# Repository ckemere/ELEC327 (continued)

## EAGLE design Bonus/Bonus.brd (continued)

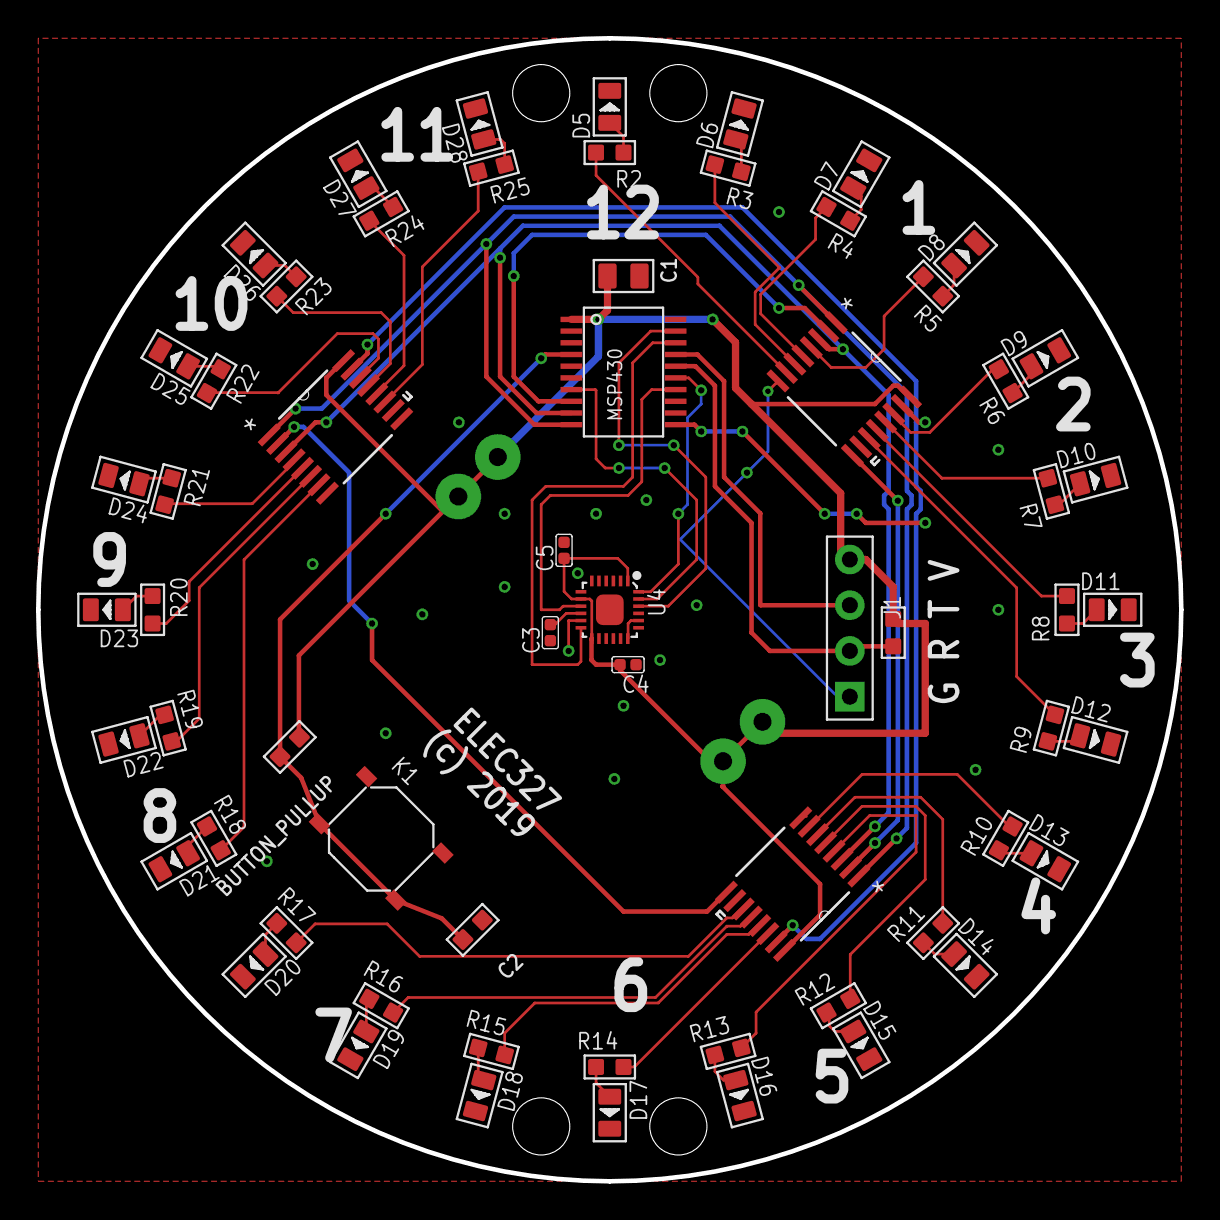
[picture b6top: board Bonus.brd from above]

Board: 2 copper layers, 63.5 x 63.5 mm, 63 parts (1 on the bottom side), 65 nets.

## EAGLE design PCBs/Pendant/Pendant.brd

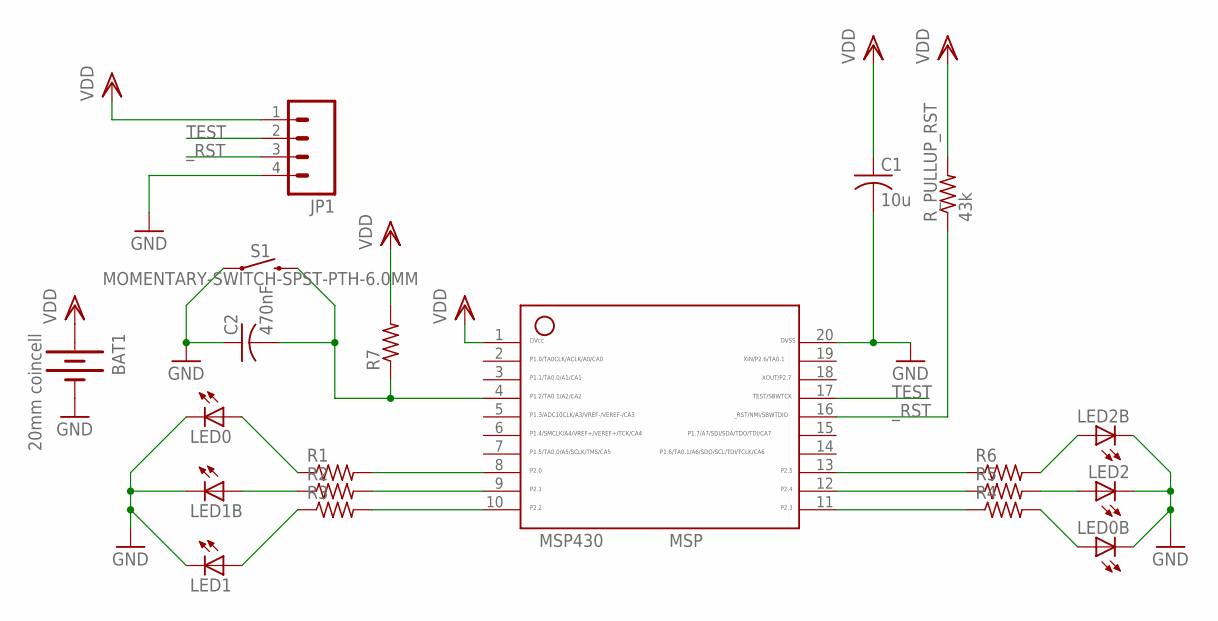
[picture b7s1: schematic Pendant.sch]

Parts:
BAT1: 20mm coincell; BATTCON_20MM_PTH_COMPACT
C1: 10u; C1206
C2: 470nF; C1206
JP1: M04LOCK; 1X04_LOCK
LED0, LED0B, LED1, LED1B, LED2, LED2B: LED1206; LED-1206
MSP430: MSP; 20_PIN
R1, R2, R3, R4, R5, R6, R7: R-US_R1206; R1206
R_PULLUP_RST: 43k; R1206
S1: MOMENTARY-SWITCH-SPST-PTH-6.0MM; TACTILE_SWITCH_PTH_6.0MM

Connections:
GND: BAT1.2 (-), C1.2, C2.1, JP1.4, LED0.C, LED0B.C, LED1.C, LED1B.C, LED2.C, LED2B.C, MSP430.20, S1.1
unnamed: MSP430.12, R5.1
unnamed: MSP430.11, R4.1
unnamed: LED2.A, R5.2
unnamed: LED0B.A, R4.2
unnamed: MSP430.13, R6.1
unnamed: LED0.A, R1.1
unnamed: LED1B.A, R2.1
unnamed: LED2B.A, R6.2
unnamed: LED1.A, R3.1
unnamed: MSP430.8, R1.2
unnamed: MSP430.9, R2.2
unnamed: MSP430.10, R3.2
unnamed: C2.2, MSP430.4, R7.1, S1.3 (2)
TEST: JP1.2, MSP430.17
VDD: BAT1.1 (+), BAT1.3 (+), BAT1.4 (+), BAT1.5 (+), C1.1, JP1.1, MSP430.1, R7.2, R_PULLUP_RST.2
_RST: JP1.3, MSP430.16, R_PULLUP_RST.1

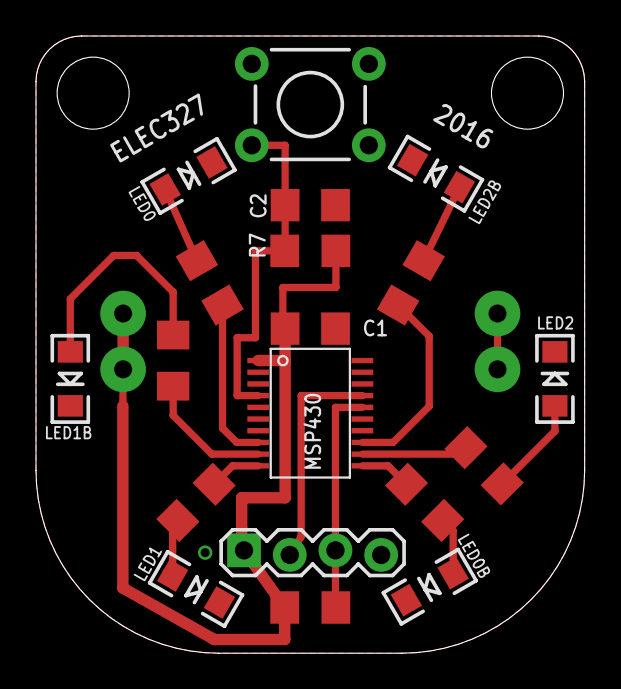
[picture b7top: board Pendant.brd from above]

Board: 2 copper layers, 30.5 x 34.3 mm, 20 parts (1 on the bottom side), 17 nets.

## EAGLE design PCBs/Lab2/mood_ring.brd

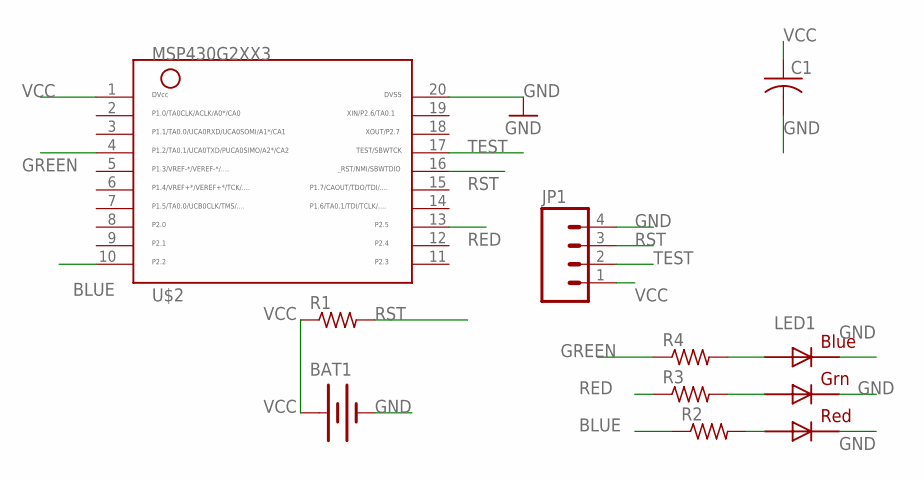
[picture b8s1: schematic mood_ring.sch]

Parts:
BAT1: BATTERYBU2032SM; BU2032SM
C1: C-USC1206; C1206
JP1: M04LOCK; 1X04_LOCK
LED1: RGBLED5050
R1, R2, R3, R4: R-US_R1206; R1206
U$2: MSP430G2XX3TSSOP; PW20

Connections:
BLUE: R2.1, U$2.10
GND: BAT1.P$2 (-), C1.2, JP1.4, LED1.4 (BLUE_C), LED1.5 (RED_C), LED1.6 (GREEN_C), U$2.20
GREEN: R4.1, U$2.4
unnamed: LED1.3 (BLUE_A), R4.2
unnamed: LED1.1 (GREEN_A), R3.2
unnamed: LED1.2 (RED_A), R2.2
RED: R3.1, U$2.13
RST: JP1.3, R1.2, U$2.16
TEST: JP1.2, U$2.17
VCC: BAT1.P$1 (+), C1.1, JP1.1, R1.1, U$2.1

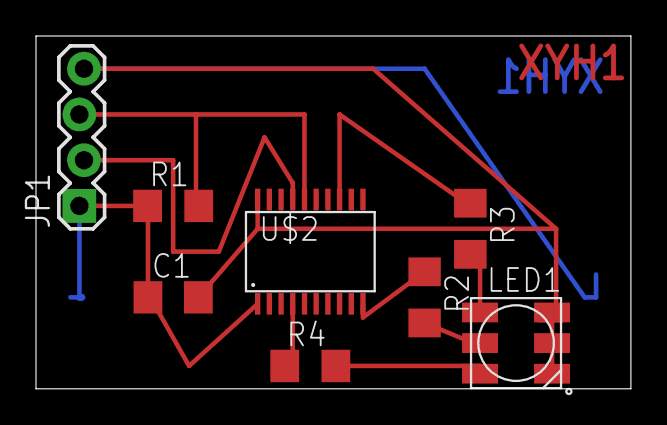
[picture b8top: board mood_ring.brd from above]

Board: 2 copper layers, 33.0 x 19.6 mm, 9 parts (1 on the bottom side), 10 nets.

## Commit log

2014-01-29 Mood ring PCB updated.
2014-01-29 Mood ring PCB updated (for real this time).
2014-01-30 Added DRC and DRU files
2014-01-31 Added Lab 2 library file
2014-02-10 Added novel CR2032 battery clip.
2015-01-30 Added data sheets and docs for MSP430s and Battery Holders
2015-01-30 Updated skeleton file for lab 2 and updated library
2015-02-02 added gitignore
2015-02-02 updated documents and added gitignore
2015-02-02 Changed MSP430 part from through-hole to SMD
2015-03-17 Added Lab 6 schematic
2015-03-17 Fixed buzzer connections
2015-03-17 added lab 2
2015-03-19 Switched to Xin Huang's schematic
2015-03-25 Changed dru file top properly generate EXCELLON_24 drill files rather than old EXCELLON
2015-03-25 Fixed VCC bug
2016-02-05 Added Labs directory, changed Lab2 to Lab3 and added datasheets
2016-02-07 Moved lab3_skeleton.c to this reposistory
2016-02-10 Added code examples and moved datasheet
2016-02-21 Moved Simon schematic to Midterm directory
2016-10-03 Added Simon schematic and board files
2016-12-28 Updated gitignore and added Pendant from 2016
2016-12-28 Updated pendant to 2017 version
2017-02-06 Updated data sheets
2017-03-16 Updated directory structure
2018-01-12 Added lab1 code
2018-01-12 Updated Pendant Eagle files
2018-01-14 Updated example file with comments
2018-01-18 Updated pendant code.
2018-01-18 Updated pendant skeleton code
2018-01-18 Updated to make epsilon harder
2018-01-21 Updated location of Pendant schematic and board files
2018-01-21 Added Bonus schematic and board files
2018-01-30 Update Lab 3 skeleton
2018-01-31 Update lab3 skeleton code to properly source ACLK from VLO
2018-02-02 Added datasheets for PCB parts
2018-02-02 Remove old unnecessary Lab 3 datasheets
2018-02-08 Added resistor for reset pin
2018-12-10 Fixed bug in bonus PCB
2018-12-10 Updated LED resistors from 1K to 300 ohms
2019-01-30 Moved Lab3 to Lab4 and added new RGB LED. Also updated Bonus PCB for manufacturing
2019-01-30 Removed old RGB LED
2019-01-30 Added back lab 3 directory and skeleton code!
2019-02-11 Updated and changed the name of CAM file. Added panelization scripts.
2019-03-15 Add updated design rules file with safer clearances to avoid pcb issues
2019-03-15 Update EAGLE library with support for MSP430 32 pin QFN package
2019-04-19 Added MSP430G2ET Launchpad app note
2019-04-19 Remove thermal vias due to massive amount of issues they cause
2019-12-31 Updated Pendant design for 2019
2020-01-23 Updated pendant.c initial template.
2020-01-31 Updated pendant template code to have LPM4 button
2020-02-06 Updated Lab 4 RGB led part
2020-03-13 Added a smd switch
2020-03-16 Added design for 2020 mailout
2020-03-17 Added holes in soldermask for stencil alignment.
2020-03-22 Added firmware for PCBs that are being sent out for 2020.
2020-04-13 Added sample code to adjust RGB LEDs based on temperature.
2020-04-16 Updated Lab 9 code to fix bug
2020-05-05 Added Simon 2020 programs
2020-05-05 Updated README for contestant E
2020-12-30 Updated pendant for 2021 (tic tac toe)
2021-01-13 Saved 2020 version of Lab2 Pendant in a new directory
2021-02-02 Updated lab1 skeleton codes for 2021
2021-02-23 Restored original 2020 pendant in directory, made a new directory for 2021 fabbed pendant, and a directory for Bonus PCB.
2021-02-24 Updates for 2021, including design for the Aisler panel for fab and giveaway.
2021-03-07 Added first bit of parsing for Panelizer
2021-03-08 Updated scripts for panelization. Now also doing stuff with GerberTools Panelizer.
2021-03-08 Updated to work properly with shifted, rotated boards.
2021-03-08 One more update to panelizer to try to deal with gergmerge repeating placements. Doesn't work, unfortunately.
2021-03-09 Added directory of temperature ADC examples.
2021-12-20 Pendant for 2022 is a 5x7 LED array
2022-01-07 Added stuff for Lab 2 PCB handout
2022-01-07 Updated panelizing script - new eagle version
2022-01-26 2021 lab structure
2022-01-27 Updated 2022 Lab 3
2022-02-07 Added accelerometer schematic for 2022
2022-02-07 Fixed connections in Lab 4 schematic
2022-02-11 Updates for Lab 5
2022-02-11 Added a few comments
2022-02-21 Added 2022 Simon board.
2022-02-21 Delete SimonPCBTest.ino
    Get rid of temptation to use Energia
2022-03-09 Added some helper code for Simon
2022-03-09 Fixed bugs in Simon template code
2022-03-09 Updated simon code
2023-01-09 2023 updates
2023-01-09 2023-Updates 2 - midterm project and libraries
2023-01-10 Added FR2433 documents
2023-01-17 Updated Lab to MSP430FR2433
2023-01-17 Update skeleton ver 1 to MSP430FR2443
2023-01-17 Update skeleton ver 2 to MSP430FR2443
2023-01-23 Updated lab1 with fix for 2023
2023-01-23 Restored scarlett's pushes
2023-01-23 And ver2 for 2023
2023-01-24 Updated for 2023
2023-01-24 Fixed #ifdef to refer to a proper label - #ifdef __MSP430FR2XX_4XX_FAMILY__
2023-02-08 Added different variant MSP430 and programming header and 1632 battery holder.
2023-02-11 Added RGB LED to library
2023-02-11 Added datasheets for parts
2023-02-16 Small update main.c
2023-02-20 Updated Numbers.c in Lab 5
2023-04-24 Added FR examples
2025-01-15 Adding stuff before switch over to M0+
2025-01-15 2024 switch to MSPM0+
2025-01-15 Purged old files
2025-01-15 Update make file to check for header dependencies and removed some spaces in code file
2025-01-15 Updated blink Makefile and code to reference a standard c and header file for class
2025-01-18 Updated docs
2025-01-21 Added code to measure pulse widths using another Launchpad
2025-01-21 Update pulsewidth measuring code to higher accuracy ROSC
2025-01-21 Updates to documentation
2025-01-21 Added Lab2 python interfacing code
2025-01-26 Updates to pulsewidth measuring program. Updated baudrate to 921600. Also measure space before pulse
2025-01-27 BufferedPulseWidth code added. (We'll remove it later.)
2025-01-27 Updated buffered. Will delete later
2025-01-27 Clocked version of code
2025-01-27 Removed buffered and original timed code
2025-01-27 Added pulsewidth binary
2025-01-27 Added a test code binary for pulsewidth
2025-01-30 Added two launchpad configuration with serial numbers
2025-01-30 Updated ClockedPulsewidth measurement. We now will assert PB6 to a 0 whenever the character 'r' is received. Connect this pin to the NRST pin so that we get a defined reset time. Second, we now repor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
2025-01-30 Updated binary
2025-01-30 Lab2 test code added
2025-02-03 Updated read_data.py for ClockedPulseWidth to have command line options
2025-02-03 Update README.md
    fixed link rendering for instruction set
2025-02-05 Added Simon 2025 PCB design
2025-02-05 Added Kicad parts library
2025-02-07 Update read_data.py
    Added a help comment for usage
2025-02-18 Updates to Kicad library for Lab 5
2025-02-21 Updated Simon PCB 2025
2025-03-24 Scripts for panelizing from KiCAD
2025-03-24 Comment for parse_panel_svg
2025-04-15 added JLC version of simon
2025-04-20 Added picture of Fabricated PCB
2025-04-20 Added Lab 5 PCB microcontroller to documents
2025-04-23 Added footprints
2025-04-23 Added LFQP48 pin device
2025-04-28 Updated parse_submissions to optionally take a grade file to gather netids
2025-05-12 Added comments to README about Launchpad serial number. Added reset option to firmware.
2025-11-26 Fixed issue with NRST pullup resistor not being connected
2026-01-12 Added for 2026
2026-01-13 Fixed gitignore for Debug
2026-01-13 Project name to lower case to match directory
2026-01-14 Added a workspace file
2026-01-14 Updated and simplified blink.c code
2026-01-14 Maybe missing dependencies added
2026-01-14 Updated project to most recent clang tools version
2026-01-14 Updated .cproject
2026-01-14 Updated Datasheet and TRM and Errata to latest
2026-01-15 Updated Lab 1 PCB files
2026-01-15 Added Lab 1 template
2026-01-15 PCB gitignore
2026-01-21 Added LED datasheets
2026-01-24 Updates for Lab 2
2026-01-27 Fixed issue with Lab2
2026-01-28 Added more project files
2026-01-28 Updated project files for blink_sleep and blink_standby
2026-02-02 Simon PCB 2026
2026-02-02 Added Simon 2026 gitignore
2026-02-03 Added template for Lab 3
2026-02-09 Updates for PCB design Lab
2026-02-09 Added MSPM0 C series doc
2026-02-09 Updated Lab 4 with connections
2026-02-09 Updated Lab4 PCB with design rules and exclusions
2026-02-11 Fixed missing VDD and GND
2026-02-11 Switched through hole footprint for RGB LED
2026-03-02 Lab 6 workspace
2026-03-12 Added Simon Template
2026-04-22 Updated pin assignments
